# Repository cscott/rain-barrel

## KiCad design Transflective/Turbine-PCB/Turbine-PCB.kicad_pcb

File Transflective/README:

To do:
1) add STEMMA QT socket(s)
2) add power regulator (5V to 3.3V)
3) add I2C resistors?
--
on base plate: (pads to regulate input to 12v (adj) / 5v / 3.3V) nah
2 STEMMA QT / 4 pin header(s)
(2) 3 pin (+5V / SIG / GND) header to supply (5V-diode drop) outside, and
 to supply 5V power
 connect to 5V backfeed on unused HUZZAH pin used in basement motor shield
Feather!
IDC connector to display
WATER_GPIO (another 5v/sig/gnd header?)
breadboard mounting
motor shield
rasp pi nano footprint -> (5V/SIG/GND) connector for snitch & routed i2c connection
----
To do: assign pin for DS_CS
Figure out how to wire-AND the pump pressure switch
  (maybe add an H-Bridge, and wire the switch to the enable input)
Routing
---
Both:
Feather!
Cap sense (i2c, 3.3V)
LCD (SPI)

Basement:
Motor Shield
Flow meter (i2c, +5V supply)
Smrty Snitch (i2c, is there a 5V supply?)
Water level sensor input?
Breadboard for smrty snitch
 (presumably 12V-ish input to motor shield, 12->5V conversion, 5V backfeed to feather through unused HUZZAH pin)

Outside:
ADS1115 A/D converter (i2c, 3.3V)
Breadboard (Vin to +/- 9V, 12V->5V switch converter, 2x 5V/SIG/GND one used to power magtag through 1N4001 diode)
 (how was the ADS1115 connected?)

Datasheets:

ADP1650 LED driver:
https://www.analog.com/media/en/technical-documentation/data-sheets/ADP1650.pdf
https://www.digikey.com/short/223nhvrn

CAP1298 Capacitive touch:
https://www.microchip.com/en-us/product/CAP1298
https://ww1.microchip.com/downloads/en/DeviceDoc/00001571B.pdf
https://www.microchip.com/content/dam/mchp/documents/OTH/ApplicationNotes/ApplicationNotes/01492A.pdf
App note: https://www.nxp.com/docs/en/application-note/AN3747.pdf

LCD panel: Displaytech 128240D FC BW-3 Graphic LCD
Digikey 1756-1047-ND or Mouser 758-S128240DFCBW-3
https://www.ebay.com/itm/293977786571
https://www.digikey.com/short/012dbnz2
https://www.seacomp.com/sites/default/files/datasheets/128240D-Series-Displaytech-Spec.pdf

Driver chip: ST7529:
https://www.sitronix.com.tw/en/products/industrial-display-driver-ic/gray-scale-stn-lcd-driver-ic/
https://www.crystalfontz.com/controllers/Sitronix/ST7529/
https://www.crystalfontz.com/controllers/Sitronix/ST7529/287/ (datasheet)

Waterproof enclosure: (haven't bought this yet)
https://www.adafruit.com/product/905
Dimensions https://cdn-shop.adafruit.com/datasheets/175mmenclosurediagram.pdf

(Alternative LED drivers:
https://www.diodes.com/assets/Datasheets/AL3644.pdf
https://www.ti.com/lit/ds/symlink/lm3642.pdf
)

Model of raspberry pi pico:
https://www.hackster.io/news/nicolo-carandini-s-3d-model-brings-an-accurate-raspberry-pi-pico-board-to-your-kicad-projects-7a2dffff9c56
Featherwing template:
https://github.com/ppelleti/FeatherWing-template-KiCad

Kicad helpers:
https://techexplorations.com/blog/kicad/blog-kicad-5-recipe-how-to-create-a-new-component-symbol/
https://techexplorations.com/kicad-4-book/index-p=112.html

BOM:                                       LCD        Rear       Have    Need
609-F314-1A7H1-11036CT-ND‎ (FPC connector)  1                              2 x
               (.01uF 0805 capacitor)      1                       8      -
732-8045-1-ND  (.1uF 0805 capacitor)       2                       9      -
732-7664-1-ND (1uF 0805 capacitor)         13                      9      4 x
732-7624-1-ND‎ (10 uF 0805 X5R capacitor)   2                              4 x
1175-1622-ND (2x7 SMD pin header)          1                              2 x
              STEMMA QT SMD                2           2          10      -
F12094CT-ND‎ (1uH 0805 inductor)            1                              2 x
RNCP0805FTD200RCT-ND (200 ohm 0805)        2                              4 x
RMCF0805JT10K0CT-ND (10k 0805)             2                              4 x
RMCF0805JT1M00CT-ND (1M 0805)              1                              2 x
CAP1298                                    1
ADP1650ACPZ-R7CT-ND (led driver)           1                       2      -
3.3V reg                                   1                      1+2     -
Feather headers                                         2         ?
SN74LVC1G02DBVRG4-ND (NOR gate)                         1                 -
  74LVC1G02W5-7DICT-ND‎                                                    1 x
2648-SC0915CT-ND (Raspberry Pi Pico)                    1                 1 x
THT 10k                                                 3       lots      -

0805 (2012 metric)

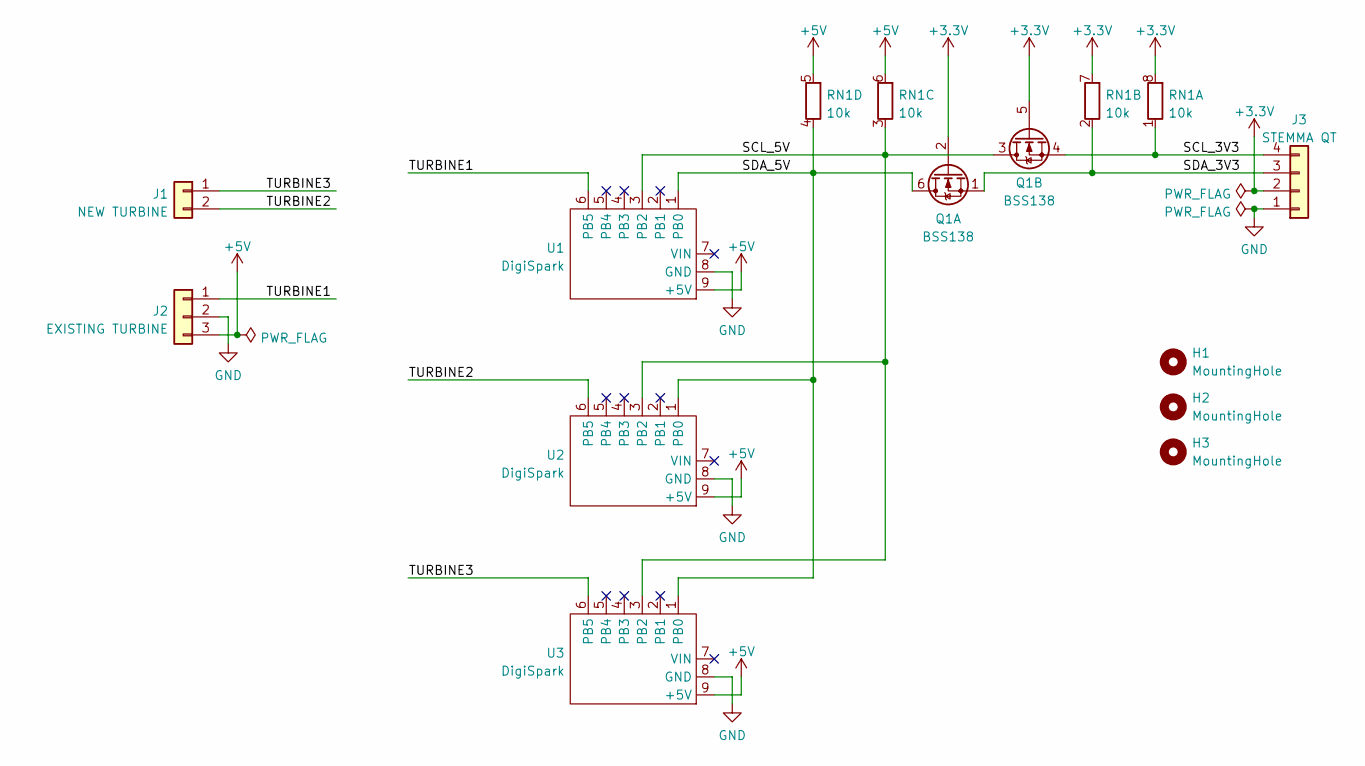
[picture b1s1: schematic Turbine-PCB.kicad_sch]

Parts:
H1, H2, H3: MountingHole; MountingHole_3.2mm_M3
J1: NEW TURBINE; JST_XH_B2B-XH-A_1x02_P2.50mm_Vertical
J2: EXISTING TURBINE; JST_XH_B3B-XH-A_1x03_P2.50mm_Vertical
J3: STEMMA QT; JST-SH-4-VERT-SMD
Q1: BSS138; SOT-363_SC-70-6_Handsoldering
RN1: 10k; R_Array_Convex_4x1206
U1, U2, U3: DigiSpark; Digispark

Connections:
+3.3V: J3.2, Q1.2 (G), Q1.5 (G), RN1.7 (R2.2), RN1.8 (R1.2)
+5V: J2.3, RN1.5 (R4.2), RN1.6 (R3.2), U1.9 (+5V), U2.9 (+5V), U3.9 (+5V)
/SCL_3V3: J3.4, Q1.4 (S), RN1.1 (R1.1)
/SCL_5V: Q1.3 (D), RN1.3 (R3.1), U1.3 (PB2), U2.3 (PB2), U3.3 (PB2)
/SDA_3V3: J3.3, Q1.1 (S), RN1.2 (R2.1)
/SDA_5V: Q1.6 (D), RN1.4 (R4.1), U1.1 (PB0), U2.1 (PB0), U3.1 (PB0)
/TURBINE1: J2.1, U1.6 (PB5)
/TURBINE2: J1.2, U2.6 (PB5)
/TURBINE3: J1.1, U3.6 (PB5)
GND: J2.2, J3.1, U1.8 (GND), U2.8 (GND), U3.8 (GND)

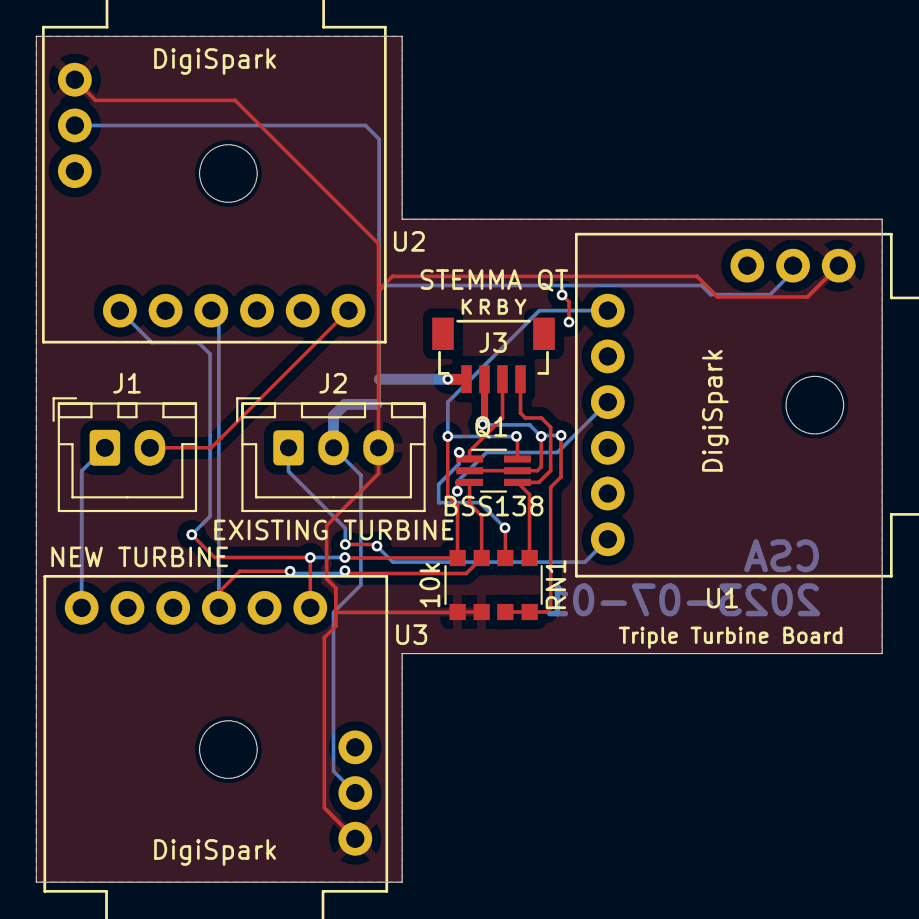
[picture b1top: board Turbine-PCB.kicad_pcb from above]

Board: 2 copper layers, 47.0 x 47.0 mm, 11 parts (0 on the bottom side), 10 nets.

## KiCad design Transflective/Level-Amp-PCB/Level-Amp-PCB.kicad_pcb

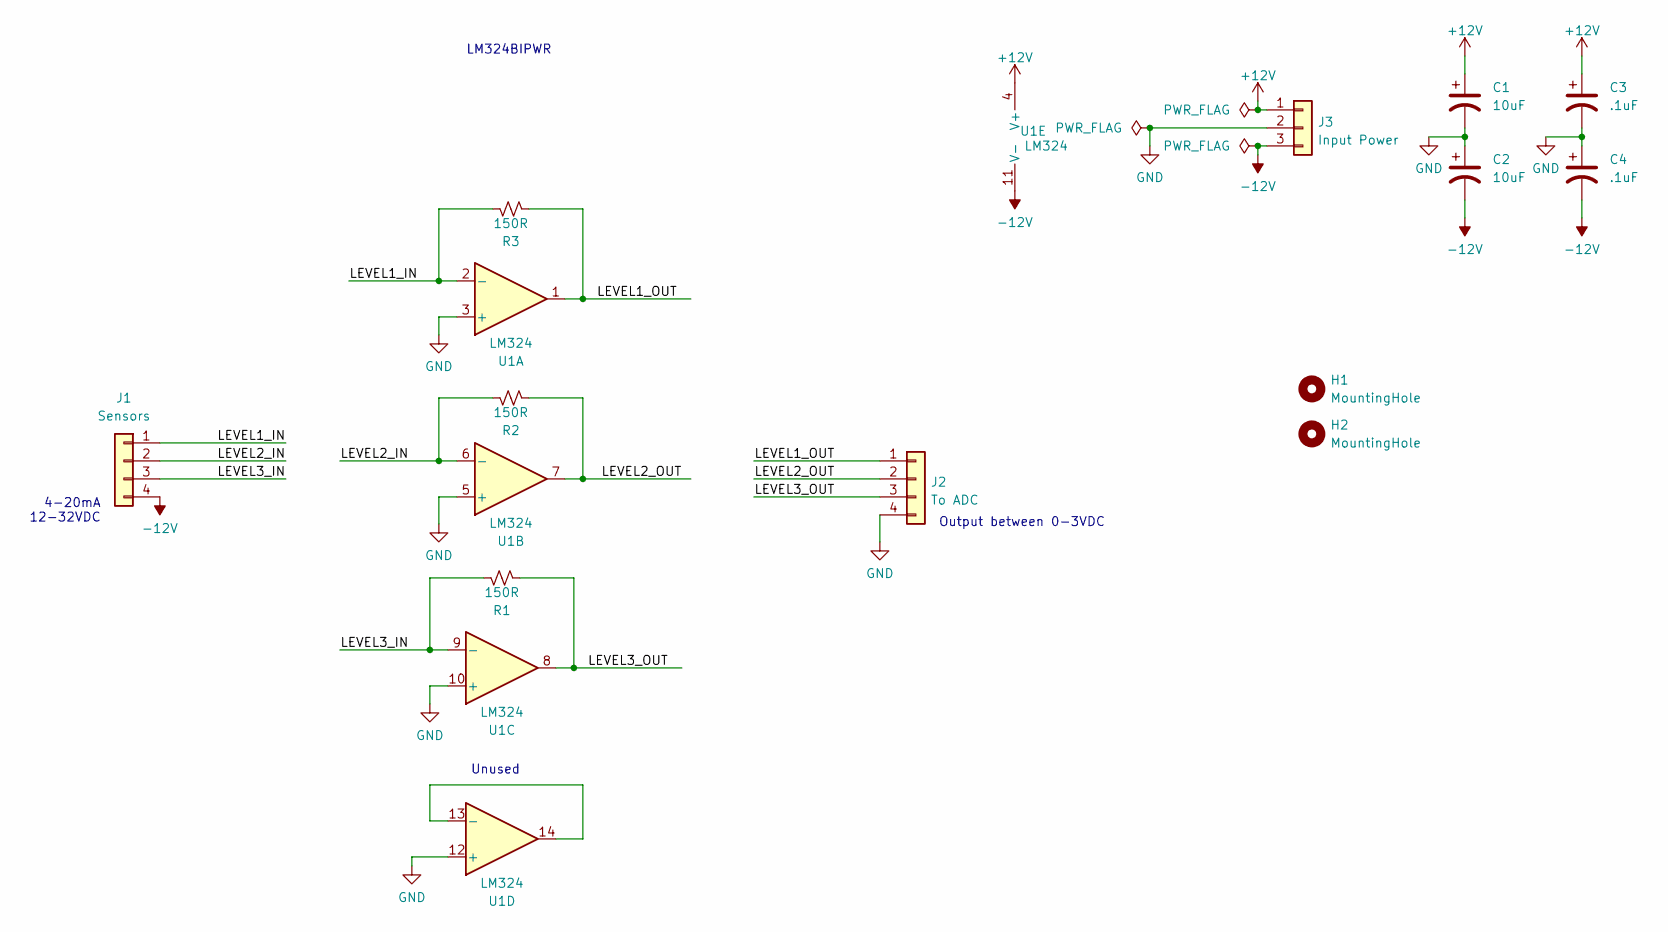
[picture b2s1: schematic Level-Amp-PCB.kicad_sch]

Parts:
C1, C2: 10uF; CP_EIA-2012-15_AVX-P_Pad1.30x1.05mm_HandSolder
C3, C4: .1uF; CP_EIA-2012-15_AVX-P_Pad1.30x1.05mm_HandSolder
H1, H2: MountingHole; MountingHole_3.2mm_M3
J1: Sensors; JST_XH_B4B-XH-A_1x04_P2.50mm_Vertical
J2: To ADC; JST_XH_B4B-XH-A_1x04_P2.50mm_Vertical
J3: Input Power; JST_XH_B3B-XH-A_1x03_P2.50mm_Vertical
R1, R2, R3: 150R; R_0805_2012Metric_Pad1.20x1.40mm_HandSolder
U1: LM324; TSSOP-14_4.4x5mm_P0.65mm

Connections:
+12V: C1.1, C3.1, J3.1, U1.4 (V+)
-12V: C2.2, C4.2, J1.4, J3.3, U1.11 (V-)
/LEVEL1_IN: J1.1, R3.1, U1.2 (-)
/LEVEL1_OUT: J2.1, R3.2, U1.1
/LEVEL2_IN: J1.2, R2.1, U1.6 (-)
/LEVEL2_OUT: J2.2, R2.2, U1.7
/LEVEL3_IN: J1.3, R1.1, U1.9 (-)
/LEVEL3_OUT: J2.3, R1.2, U1.8
GND: C1.2, C2.1, C3.2, C4.1, J2.4, J3.2, U1.3 (+), U1.5 (+), U1.10 (+), U1.12 (+)
unnamed: U1.13 (-), U1.14

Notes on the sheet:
4-20mA 12-32VDC
Output between 0-3VDC
LM324BIPWR
Unused

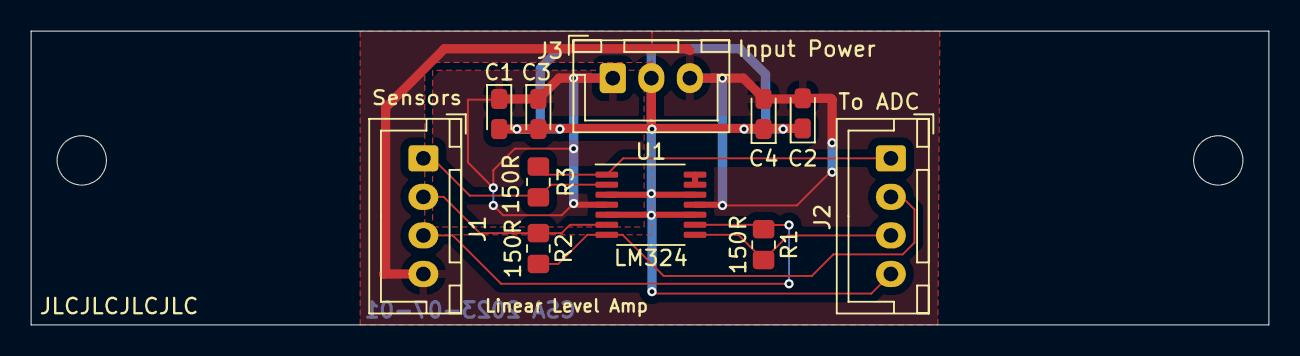
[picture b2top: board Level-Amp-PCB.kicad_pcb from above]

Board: 2 copper layers, 80.3 x 19.1 mm, 13 parts (0 on the bottom side), 10 nets.

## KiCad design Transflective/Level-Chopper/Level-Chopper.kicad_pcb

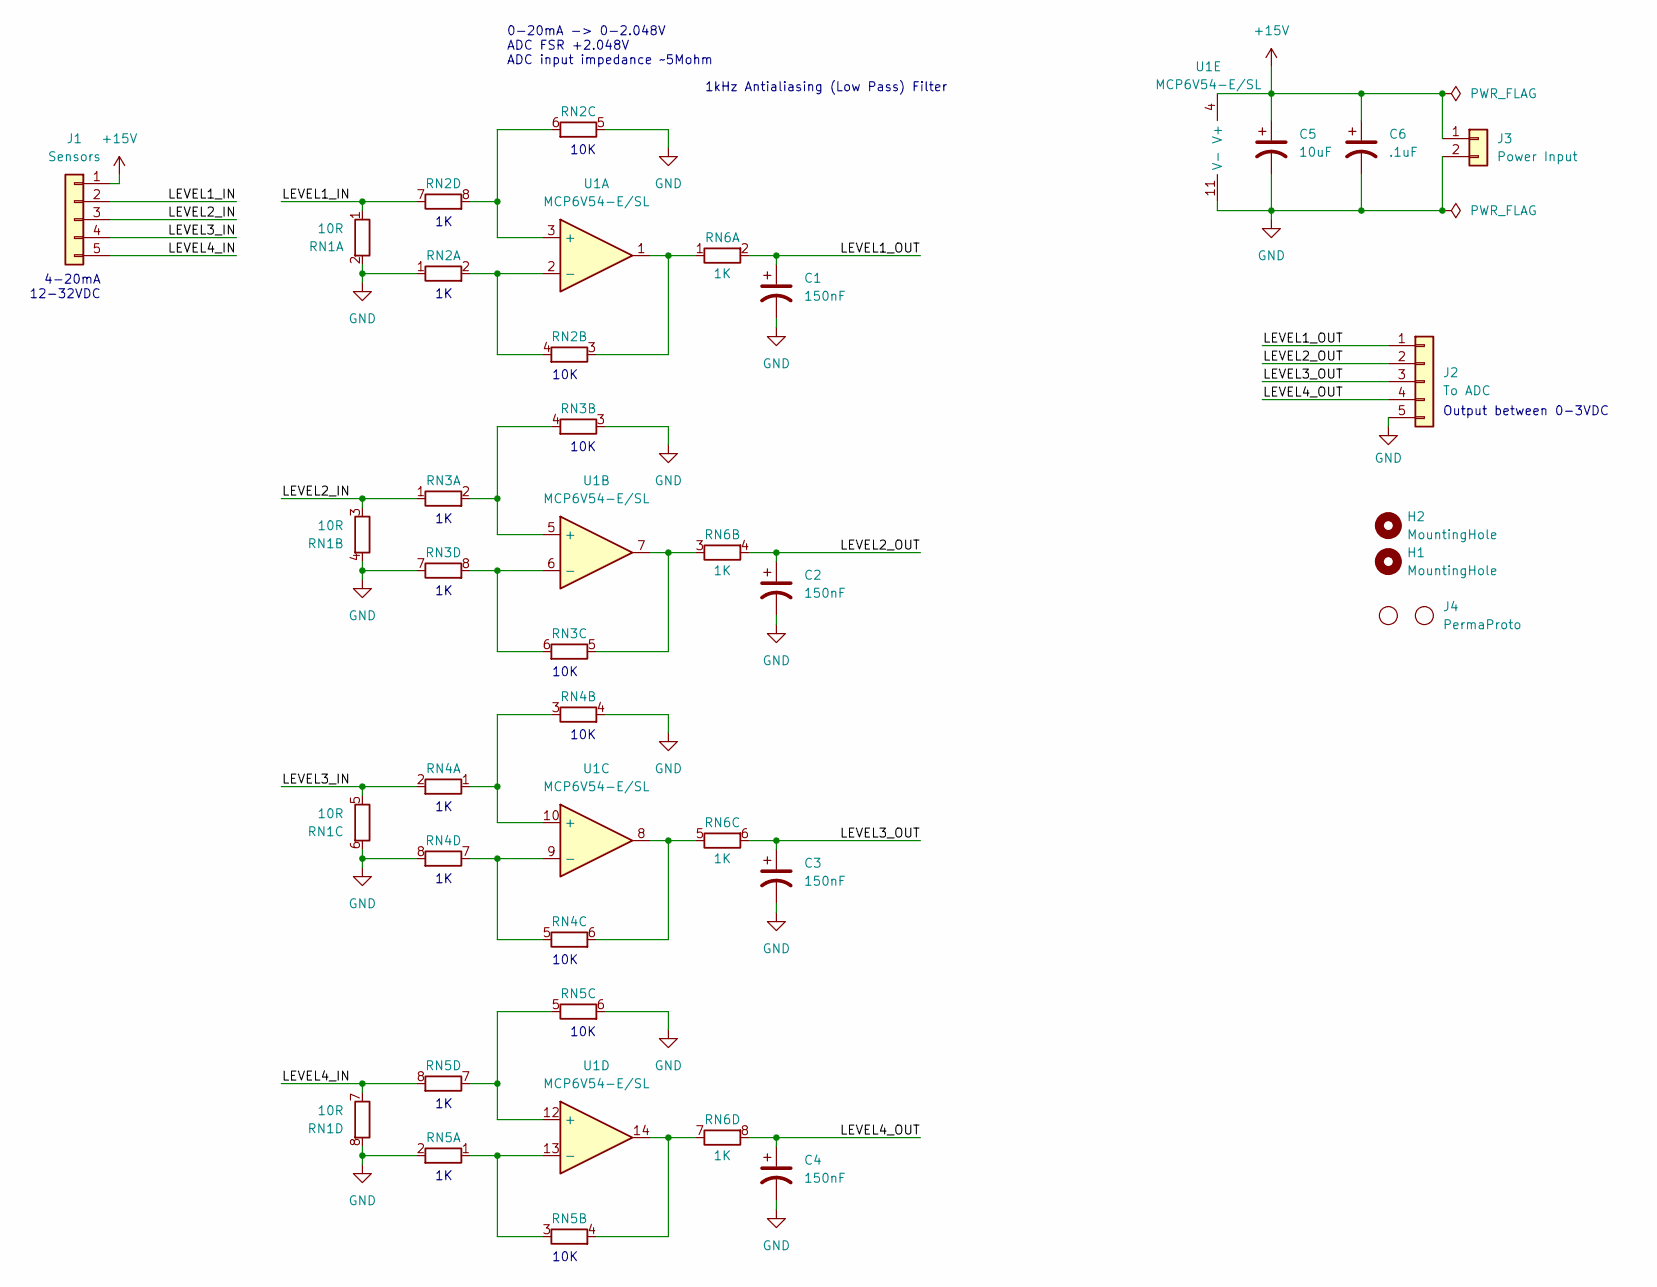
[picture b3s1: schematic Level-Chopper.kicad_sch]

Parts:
C1, C2, C3, C4: 150nF; CP_EIA-2012-15_AVX-P_Pad1.30x1.05mm_HandSolder
C5: 10uF; CP_EIA-2012-15_AVX-P_Pad1.30x1.05mm_HandSolder
C6: .1uF; CP_EIA-2012-15_AVX-P_Pad1.30x1.05mm_HandSolder
H1, H2: MountingHole; MountingHole_3.2mm_M3
J1: Sensors; JST_XH_B5B-XH-A_1x05_P2.50mm_Vertical
J2: To ADC; JST_XH_B5B-XH-A_1x05_P2.50mm_Vertical
J3: Power Input; JST_XH_B2B-XH-A_1x02_P2.50mm_Vertical
J4: PermaProto
RN1: 10R; RES_ACAS_0612_VIS
RN2, RN3, RN4, RN5: 1K/10k; RES_ACAS_0612_VIS
RN6: 1K; RES_ACAS_0612_VIS
U1: MCP6V54-E/SL; SOIC-14_3.9x8.7mm_P1.27mm

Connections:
+15V: C5.1, C6.1, J1.1, J3.1, U1.4 (V+)
/LEVEL1_IN: J1.2, RN1.1 (R1.1), RN2.7 (R4.1)
/LEVEL1_OUT: C1.1, J2.1, RN6.2 (R1.2)
/LEVEL2_IN: J1.3, RN1.3 (R2.1), RN3.1 (R1.1)
/LEVEL2_OUT: C2.1, J2.2, RN6.4 (R2.2)
/LEVEL3_IN: J1.4, RN1.5 (R3.1), RN4.2 (R1.2)
/LEVEL3_OUT: C3.1, J2.3, RN6.6 (R3.2)
/LEVEL4_IN: J1.5, RN1.7 (R4.1), RN5.8 (R4.2)
/LEVEL4_OUT: C4.1, J2.4, RN6.8 (R4.2)
GND: C1.2, C2.2, C3.2, C4.2, C5.2, C6.2, J2.5, J3.2, RN1.2 (R1.2), RN1.4 (R2.2), RN1.6 (R3.2), RN1.8 (R4.2), RN2.1 (R1.1), RN2.5 (R3.1), RN3.3 (R2.1), RN3.7 (R4.1), RN4.4 (R2.2), RN4.8 (R4.2), RN5.2 (R1.2), RN5.6 (R3.2), U1.11 (V-)
unnamed: RN2.2 (R1.2), RN2.4 (R2.2), U1.2 (-)
unnamed: RN2.3 (R2.1), RN6.1 (R1.1), U1.1
unnamed: RN2.6 (R3.2), RN2.8 (R4.2), U1.3 (+)
unnamed: RN3.2 (R1.2), RN3.4 (R2.2), U1.5 (+)
unnamed: RN3.5 (R3.1), RN6.3 (R2.1), U1.7
unnamed: RN3.6 (R3.2), RN3.8 (R4.2), U1.6 (-)
unnamed: RN4.1 (R1.1), RN4.3 (R2.1), U1.10 (+)
unnamed: RN4.5 (R3.1), RN4.7 (R4.1), U1.9 (-)
unnamed: RN4.6 (R3.2), RN6.5 (R3.1), U1.8
unnamed: RN5.1 (R1.1), RN5.3 (R2.1), U1.13 (-)
unnamed: RN5.4 (R2.2), RN6.7 (R4.1), U1.14
unnamed: RN5.5 (R3.1), RN5.7 (R4.1), U1.12 (+)

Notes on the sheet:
0-20mA -> 0-2.048V ADC FSR +2.048V ADC input impedance ~5Mohm
1kHz Antialiasing (Low Pass) Filter
10K
4-20mA 12-32VDC
Output between 0-3VDC

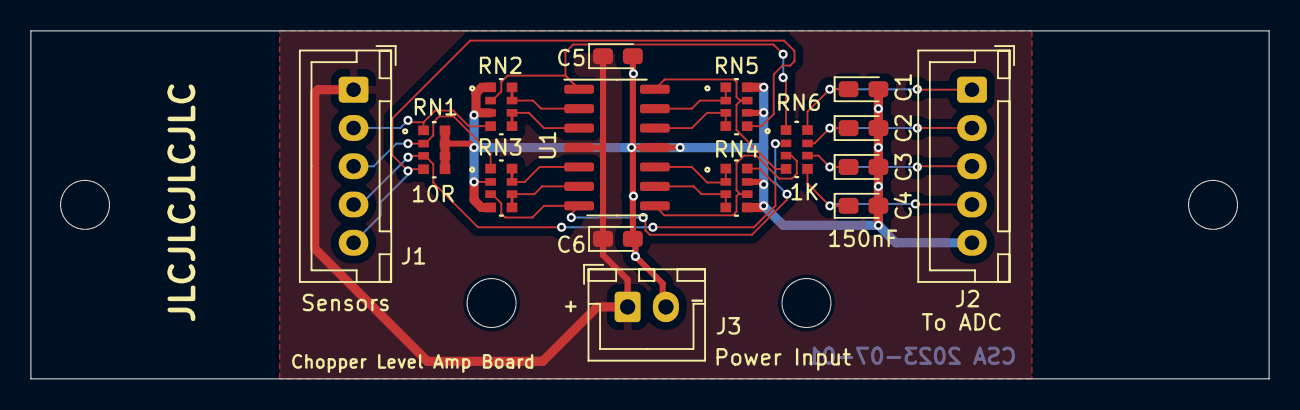
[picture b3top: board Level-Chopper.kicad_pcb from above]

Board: 2 copper layers, 80.9 x 22.7 mm, 19 parts (0 on the bottom side), 22 nets.

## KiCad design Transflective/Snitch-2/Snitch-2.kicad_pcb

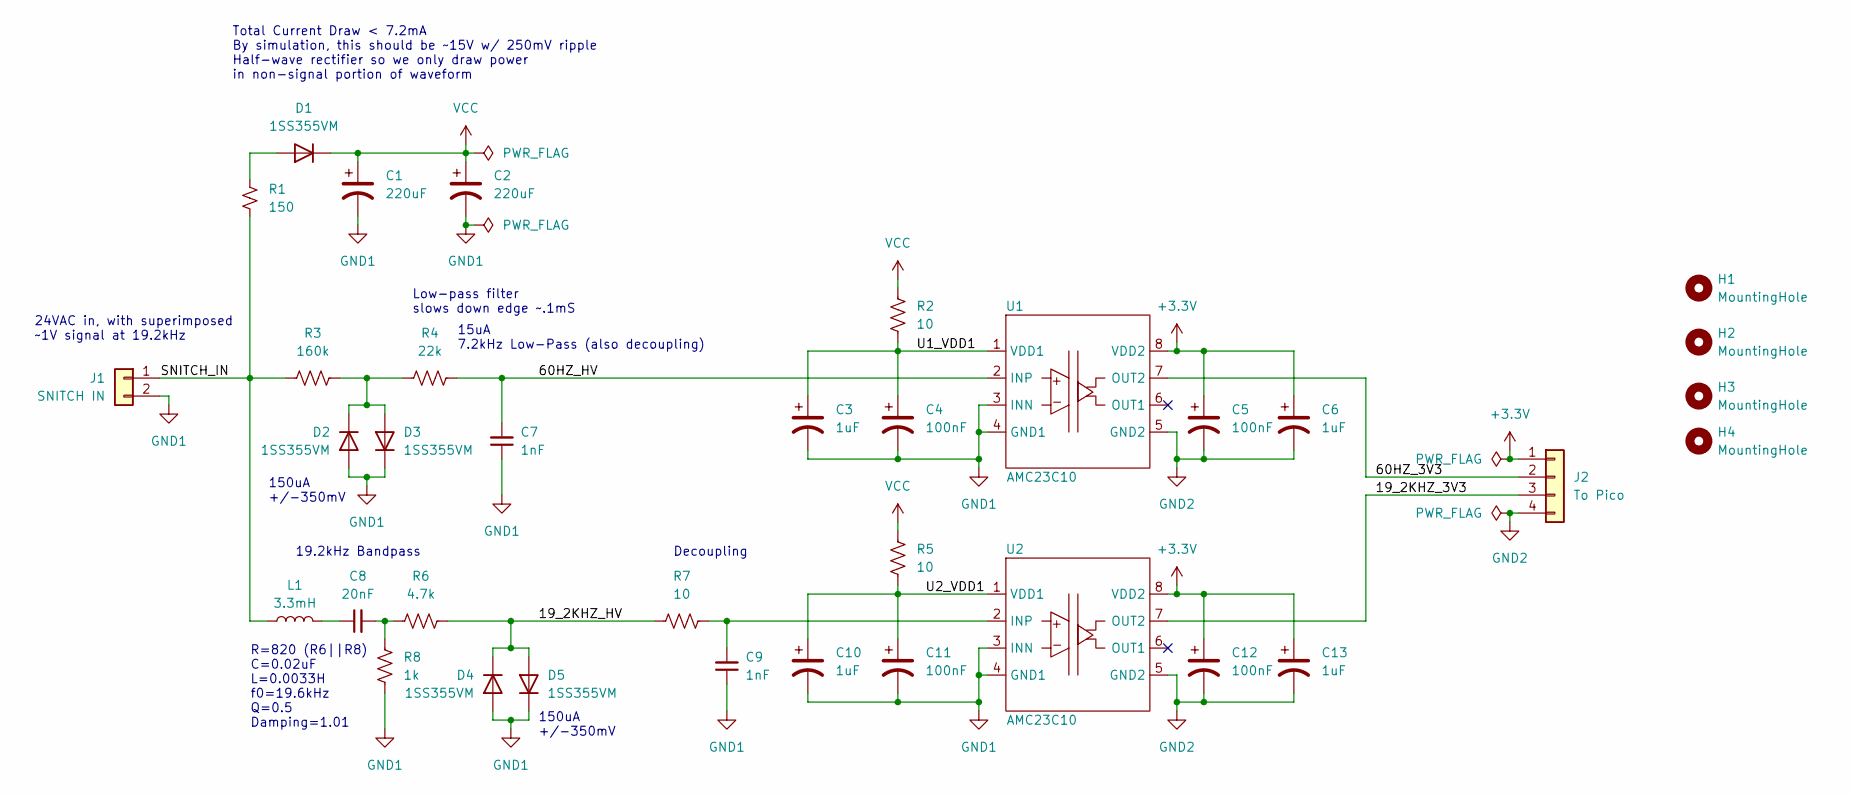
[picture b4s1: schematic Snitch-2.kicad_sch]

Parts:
C1, C2: 220uF; CP_Elec_13.7x13
C3, C6, C10, C13: 1uF; C_0805_2012Metric_Pad1.18x1.45mm_HandSolder
C4, C5, C11, C12: 100nF; C_0805_2012Metric_Pad1.18x1.45mm_HandSolder
C7, C9: 1nF; C_0805_2012Metric_Pad1.18x1.45mm_HandSolder
C8: 20nF; C_0805_2012Metric_Pad1.18x1.45mm_HandSolder
D1, D2, D3, D4, D5: 1SS355VM; D_SOD-323F
H1, H2, H3, H4: MountingHole; MountingHole_3.2mm_M3
J1: SNITCH IN; JST_XH_B2B-XH-A_1x02_P2.50mm_Vertical
J2: To Pico; JST_XH_B4B-XH-A_1x04_P2.50mm_Vertical
L1: 3.3mH; L_Bourns_SDR0805
R1: 150; R_0805_2012Metric_Pad1.20x1.40mm_HandSolder
R2, R5, R7: 10; R_0805_2012Metric_Pad1.20x1.40mm_HandSolder
R3: 160k; R_0805_2012Metric_Pad1.20x1.40mm_HandSolder
R4: 22k; R_0805_2012Metric_Pad1.20x1.40mm_HandSolder
R6: 4.7k; R_0805_2012Metric_Pad1.20x1.40mm_HandSolder
R8: 1k; R_0805_2012Metric_Pad1.20x1.40mm_HandSolder
U1, U2: AMC23C10; SOIC-8_7.5x5.85mm_P1.27mm

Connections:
+3.3V: C5.1, C6.1, C12.1, C13.1, J2.1, U1.8 (VDD2), U2.8 (VDD2)
/19_2KHZ_3V3: J2.3, U2.7 (OUT2)
/19_2KHZ_HV: D4.1 (K), D5.2 (A), R6.2, R7.1
/60HZ_3V3: J2.2, U1.7 (OUT2)
/60HZ_HV: C7.2, R4.2, U1.2 (INP)
/SNITCH_IN: J1.1, L1.1, R1.2, R3.1
/U1_VDD1: C3.1, C4.1, R2.1, U1.1 (VDD1)
/U2_VDD1: C10.1, C11.1, R5.1, U2.1 (VDD1)
GND1: C1.2, C2.2, C3.2, C4.2, C7.1, C9.1, C10.2, C11.2, D2.2 (A), D3.1 (K), D4.2 (A), D5.1 (K), J1.2, R8.1, U1.3 (INN), U1.4 (GND1), U2.3 (INN), U2.4 (GND1)
GND2: C5.2, C6.2, C12.2, C13.2, J2.4, U1.5 (GND2), U2.5 (GND2)
unnamed: C8.1, L1.2
unnamed: C8.2, R6.1, R8.2
unnamed: D1.2 (A), R1.1
unnamed: D2.1 (K), D3.2 (A), R3.2, R4.1
unnamed: C9.2, R7.2, U2.2 (INP)
VCC: C1.1, C2.1, D1.1 (K), R2.2, R5.2

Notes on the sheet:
R=820 (R6||R8) C=0.02uF L=0.0033H f0=19.6kHz Q=0.5 Damping=1.01
24VAC in, with superimposed ~1V signal at 19.2kHz
Total Current Draw < 7.2mA By simulation, this should be ~15V w/ 250mV ripple Half-wave rectifier so we only draw power in non-signal portion of waveform
Decoupling
Low-pass filter slows down edge ~.1mS
15uA 7.2kHz Low-Pass (also decoupling)
150uA +/-350mV
19.2kHz Bandpass

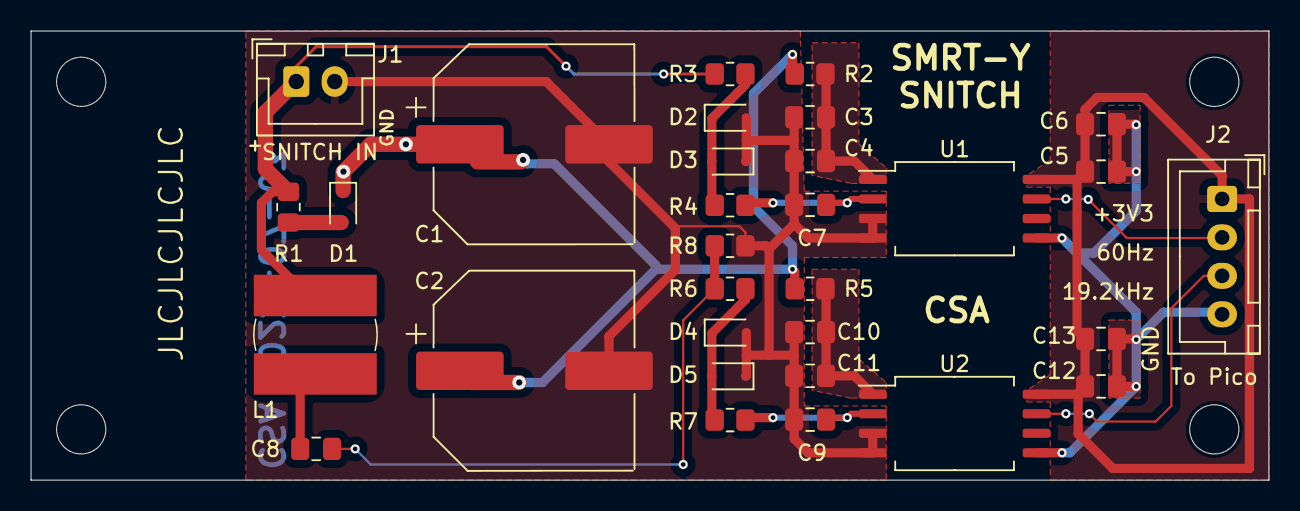
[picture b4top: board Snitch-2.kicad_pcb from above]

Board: 2 copper layers, 80.5 x 29.2 mm, 35 parts (0 on the bottom side), 16 nets.

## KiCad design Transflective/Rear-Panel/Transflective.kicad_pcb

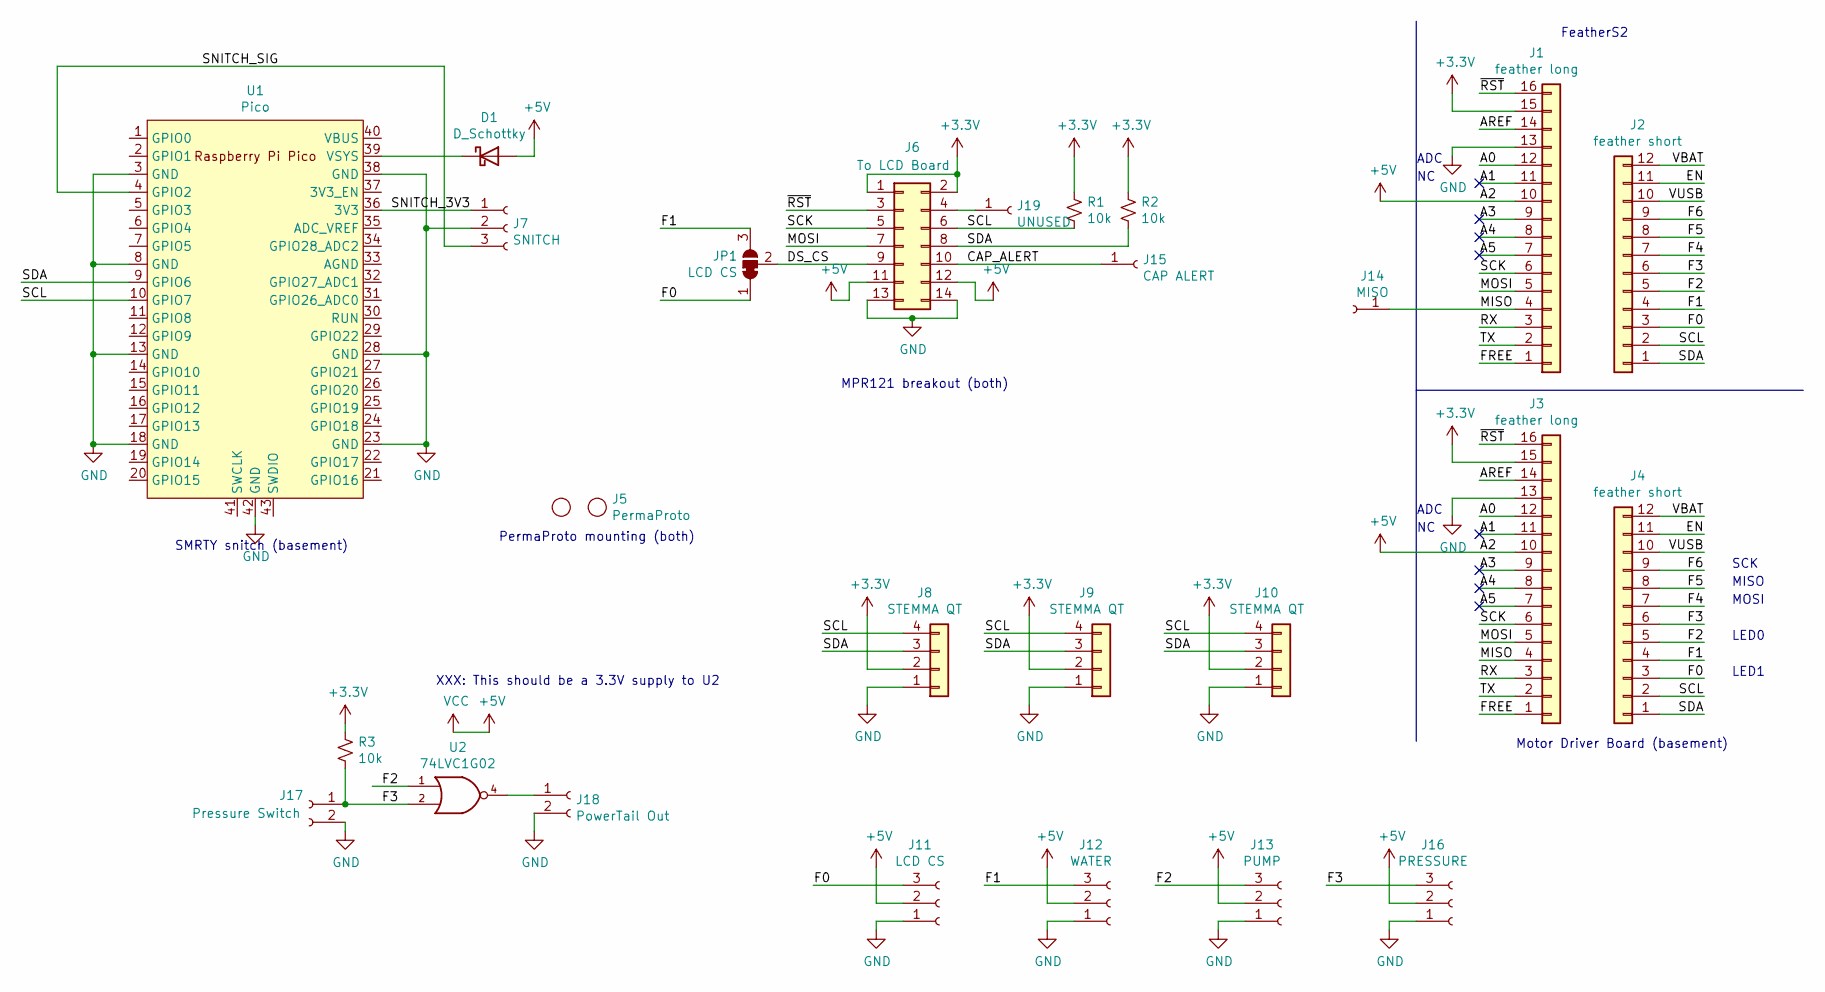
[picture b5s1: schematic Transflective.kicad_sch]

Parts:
D1: D_Schottky; D_DO-41_SOD81_P10.16mm_Horizontal
J1, J3: feather long; PinHeader_1x16_P2.54mm_Vertical
J2, J4: feather short; PinHeader_1x12_P2.54mm_Vertical
J5: PermaProto
J6: To LCD Board; IDC-Header_2x07_P2.54mm_Vertical
J7: SNITCH; JST_XH_B03B-XH-AM_1x03_P2.50mm_Vertical
J8, J9: STEMMA QT; JST-SH-4-VERT-SMD
J10: STEMMA QT; JST_XH_B04B-XH-AM_1x04_P2.50mm_Vertical
J11: LCD CS; JST_XH_B03B-XH-AM_1x03_P2.50mm_Vertical
J12: WATER; JST_XH_B03B-XH-AM_1x03_P2.50mm_Vertical
J13: PUMP; JST_XH_B03B-XH-AM_1x03_P2.50mm_Vertical
J14: MISO; PinHeader_1x01_P2.54mm_Vertical
J15: CAP ALERT; PinHeader_1x01_P2.54mm_Vertical
J16: PRESSURE; JST_XH_B03B-XH-AM_1x03_P2.50mm_Vertical
J17: Pressure Switch; JST_XH_B02B-XH-AM_1x02_P2.50mm_Vertical
J18: PowerTail Out; JST_XH_B02B-XH-AM_1x02_P2.50mm_Vertical
J19: UNUSED; PinHeader_1x01_P2.54mm_Vertical
JP1: LCD CS; SolderJumper-3_P1.3mm_Bridged2Bar12_RoundedPad1.0x1.5mm
R1, R2, R3: 10k; R_Axial_DIN0207_L6.3mm_D2.5mm_P10.16mm_Horizontal
U1: Pico; RPi_Pico_SMD_TH
U2: 74LVC1G02; SOT-23-5_HandSoldering

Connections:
+3V3: J1.15, J3.15, J6.1, J6.2, J8.2, J9.2, J10.2, R1.1, R2.1, R3.1
+5V: D1.2 (A), J1.10, J3.10, J6.11, J6.12, J11.2, J12.2, J13.2, J16.2, U2.5 (VCC)
/A0: J1.12, J3.12
/A1: J1.11, J3.11
/A3: J1.9, J3.9
/A4: J1.8, J3.8
/A5: J1.7, J3.7
/AREF: J1.14, J3.14
/CAP_ALERT: J6.10, J15.1
/DS_CS: J6.9, JP1.2 (C)
/EN: J2.11, J4.11
/F0: J2.3, J4.3, J11.3, JP1.1 (A)
/F1: J2.4, J4.4, J12.3, JP1.3 (B)
/F2: J2.5, J4.5, J13.3, U2.1
/F3: J2.6, J4.6, J16.3, J17.1, R3.2, U2.2
/F4: J2.7, J4.7
/F5: J2.8, J4.8
/F6: J2.9, J4.9
/FREE: J1.1, J3.1
/MISO: J1.4, J3.4, J14.1
/MOSI: J1.5, J3.5, J6.7
/RX: J1.3, J3.3
/SCK: J1.6, J3.6, J6.5
/SCL: J2.2, J4.2, J6.6, J8.4, J9.4, J10.4, R1.2, U1.10 (GPIO7)
/SDA: J2.1, J4.1, J6.8, J8.3, J9.3, J10.3, R2.2, U1.9 (GPIO6)
/SNITCH_3V3: J7.1, U1.36 (3V3)
/SNITCH_SIG: J7.3, U1.4 (GPIO2)
/TX: J1.2, J3.2
/VBAT: J2.12, J4.12
/VUSB: J2.10, J4.10
/~RST: J1.16, J3.16, J6.3
GND: J1.13, J3.13, J6.13, J6.14, J7.2, J8.1, J9.1, J10.1, J11.1, J12.1, J13.1, J16.1, J17.2, J18.2, U1.3 (GND), U1.8 (GND), U1.13 (GND), U1.18 (GND), U1.23 (GND), U1.28 (GND), U1.38 (GND), U1.42 (GND), U2.3 (GND)
unnamed: D1.1 (K), U1.39 (VSYS)
unnamed: J18.1, U2.4
unnamed: J6.4, J19.1

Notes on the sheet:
XXX: This should be a 3.3V supply to U2
FeatherS2
LED0
MISO
LED1
MOSI
ADC
Motor Driver Board (basement)
SMRTY snitch (basement)
MPR121 breakout (both)
PermaProto mounting (both)
SCK

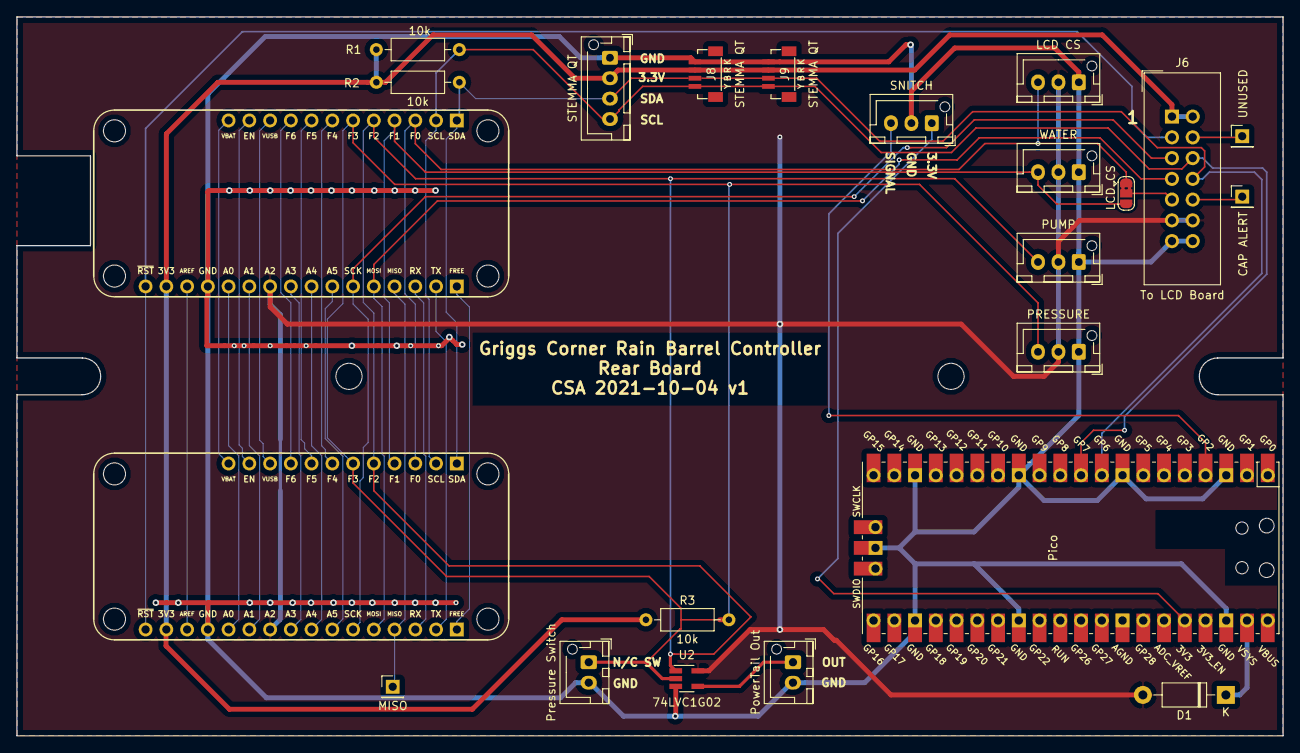
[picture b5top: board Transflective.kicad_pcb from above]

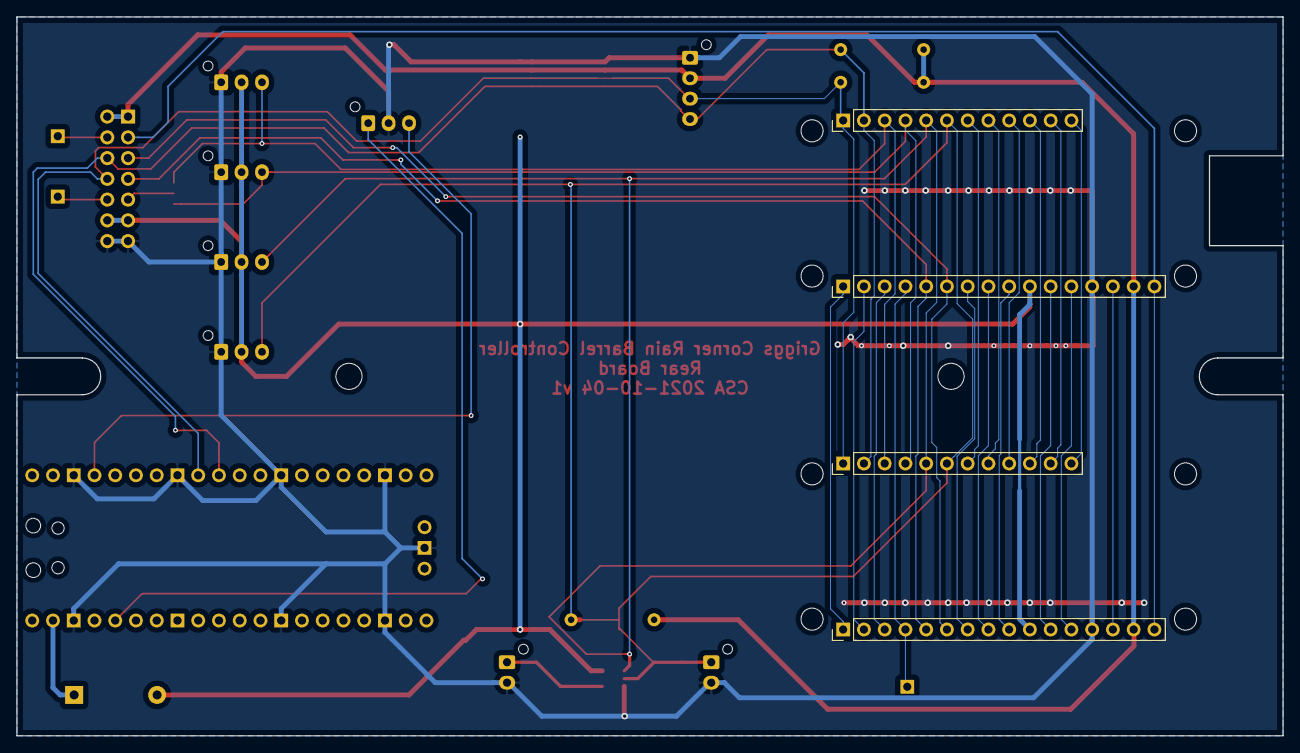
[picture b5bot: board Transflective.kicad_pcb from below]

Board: 2 copper layers, 155.0 x 88.0 mm, 26 parts (4 on the bottom side), 35 nets.

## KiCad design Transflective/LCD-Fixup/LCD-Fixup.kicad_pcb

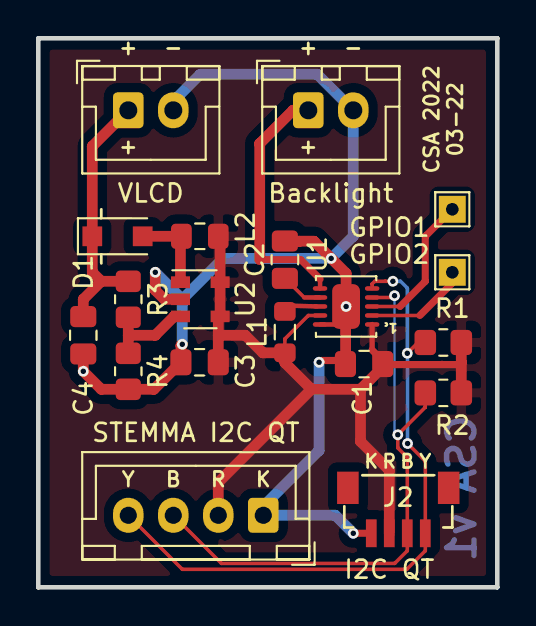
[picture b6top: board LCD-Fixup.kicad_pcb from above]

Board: 2 copper layers, 25.5 x 30.5 mm, 19 parts (0 on the bottom side), 12 nets.

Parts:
C1, C2: 10uF; C_0805_2012Metric_Pad1.18x1.45mm_HandSolder
C3, C4: 1uF; C_0805_2012Metric_Pad1.18x1.45mm_HandSolder
D1: 1N5819; D_SOD-123F
J1: STEMMA I2C QT; JST_XH_B4B-XH-A_1x04_P2.50mm_Vertical
J2: I2C QT; JST-SH-4-VERT-SMD
J3: Backlight; JST_XH_B2B-XH-A_1x02_P2.50mm_Vertical
J4: VLCD; JST_XH_B2B-XH-A_1x02_P2.50mm_Vertical
L1: 1.0uH; L_0805_2012Metric_Pad1.05x1.20mm_HandSolder
L2: 10uH; L_0805_2012Metric_Pad1.15x1.40mm_HandSolder
R1, R2: 10k; R_0805_2012Metric_Pad1.20x1.40mm_HandSolder
R3: 59k; R_0805_2012Metric_Pad1.20x1.40mm_HandSolder
R4: 4.7k; R_0805_2012Metric_Pad1.20x1.40mm_HandSolder
TP1: GPIO1; TestPoint_THTPad_1.5x1.5mm_Drill0.7mm
TP2: GPIO2; TestPoint_THTPad_1.5x1.5mm_Drill0.7mm
U1: ADP1650ACPZ-R7
U2: AP3012; SOT-23-5

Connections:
+3V3: C1.1, C3.1, J1.2, J2.2, L1.1, L2.1, R1.1, R2.1, U1.1, U1.9, U2.4, U2.5
/CAP_CLK: J1.4, J2.4, R1.2, U1.5
/CAP_DAT: J1.3, J2.3, R2.2, U1.4
/GPIO1: TP1.1, U1.3
/GPIO2: TP2.1, U1.2
GND: C1.2, C2.2, C3.2, C4.2, J1.1, J2.1, J3.2, J4.2, R4.2, U1.10, U1.11, U2.2
unnamed: C2.1, U1.7
unnamed: D1.2, L2.2, U2.1
unnamed: J3.1, U1.6
unnamed: L1.2, U1.8
unnamed: R3.2, R4.1, U2.3
Vdrive: C4.1, D1.1, J4.1, R3.1

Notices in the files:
parts and their libraries:
Copyright 2021 Accelerated Designs. All rights reserved.
